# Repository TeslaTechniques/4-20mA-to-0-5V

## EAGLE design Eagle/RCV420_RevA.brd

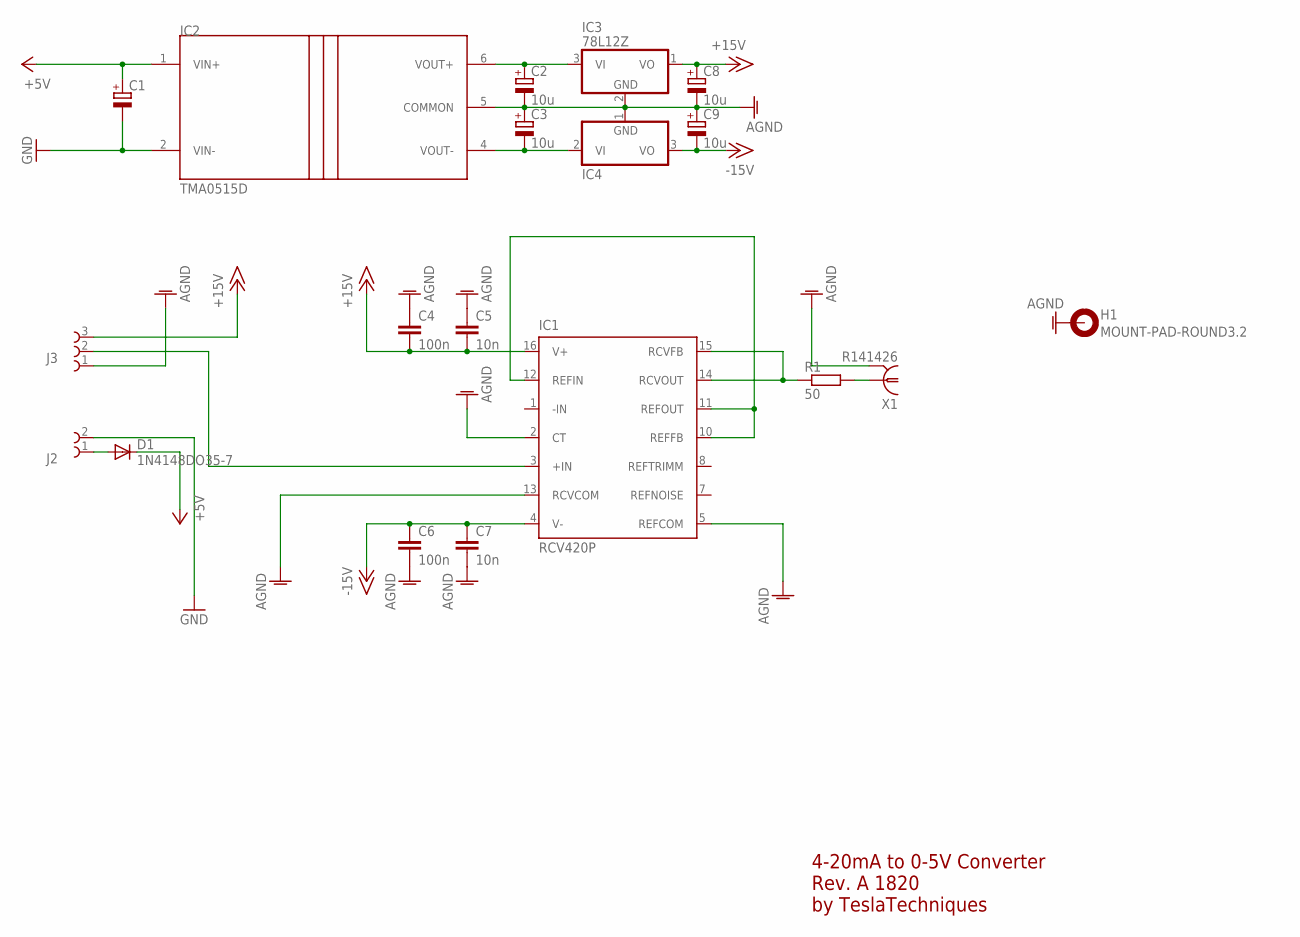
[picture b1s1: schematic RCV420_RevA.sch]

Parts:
C1: CPOL-EUE2.5-5; E2,5-5
C2, C3, C8, C9: 10u; E2,5-5
C4, C6: 100n; C025-025X050
C5, C7: 10n; C025-025X050
D1: 1N4148DO35-7; DO35-7
H1: MOUNT-PAD-ROUND3.2; 3,2-PAD
IC1: RCV420P; DIL16
IC2: TMA0515D; SIP7
IC3: 78L12Z; TO92
IC4: 7912L; TO92
J2: 691111710002
J3: 691111710003
R1: 50; 0411/12
X1: R141426

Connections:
+5V: C1.+, D1.C, IC2.1 (VIN+)
+15V: C4.2, C5.2, C8.+, IC1.16 (V+), IC3.1 (VO), J3.3
-15V: C6.1, C7.1, C9.-, IC1.4 (V-), IC4.3 (VO)
AGND: C2.-, C3.+, C4.1, C5.1, C6.2, C7.2, C8.-, C9.+, H1.B3,2, IC1.2 (CT), IC1.5 (REFCOM), IC1.13 (RCVCOM), IC2.5 (COMMON), IC3.2 (GND), IC4.1 (GND), J3.1, X1.2, X1.3 (2), X1.4 (2), X1.5 (2)
GND: C1.-, IC2.2 (VIN-), J2.2
unnamed: IC1.3 (+IN), J3.2
unnamed: C2.+, IC2.6 (VOUT+), IC3.3 (VI)
unnamed: C3.-, IC2.4 (VOUT-), IC4.2 (VI)
unnamed: D1.A, J2.1
unnamed: IC1.14 (RCVOUT), IC1.15 (RCVFB), R1.1
unnamed: IC1.10 (REFFB), IC1.11 (REFOUT), IC1.12 (REFIN)
unnamed: R1.2, X1.1

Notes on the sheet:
4-20mA to 0-5V Converter Rev. A 1820 by TeslaTechniques

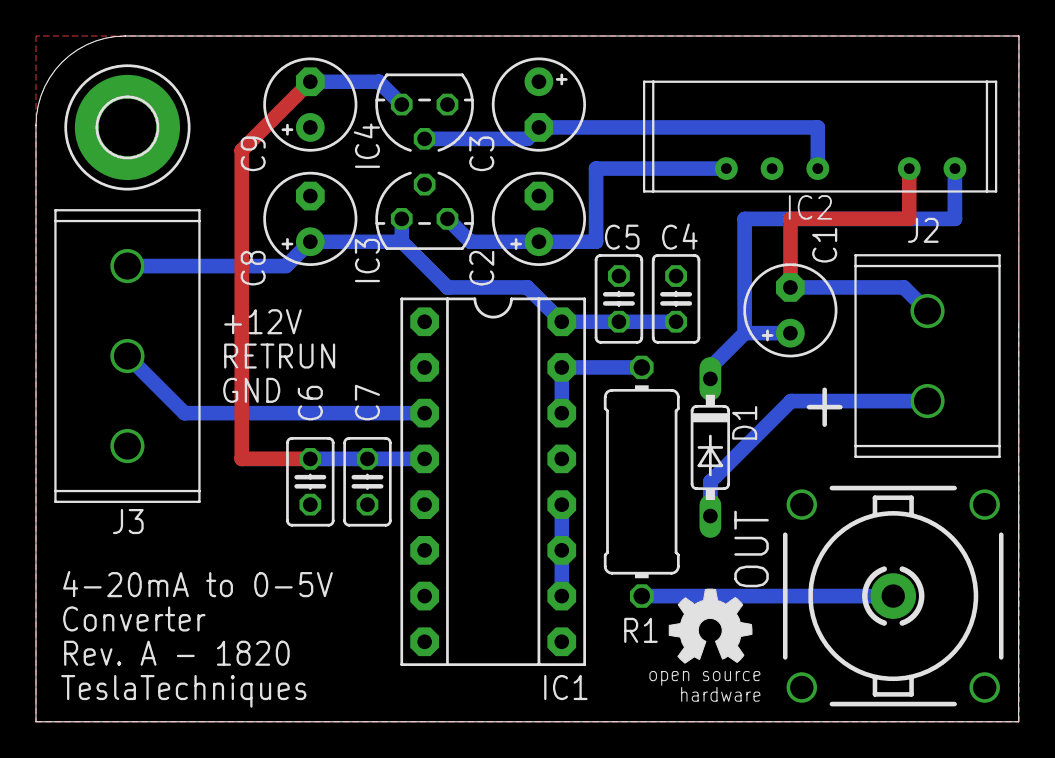
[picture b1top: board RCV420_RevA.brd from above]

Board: 2 copper layers, 54.6 x 38.1 mm, 20 parts (0 on the bottom side), 12 nets.

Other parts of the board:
U$1: OSHW_5MM

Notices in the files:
parts and their libraries:
EAGLE-TERMINAL_BLOCKS-rev16e: Copyright: Würth Elektronik
